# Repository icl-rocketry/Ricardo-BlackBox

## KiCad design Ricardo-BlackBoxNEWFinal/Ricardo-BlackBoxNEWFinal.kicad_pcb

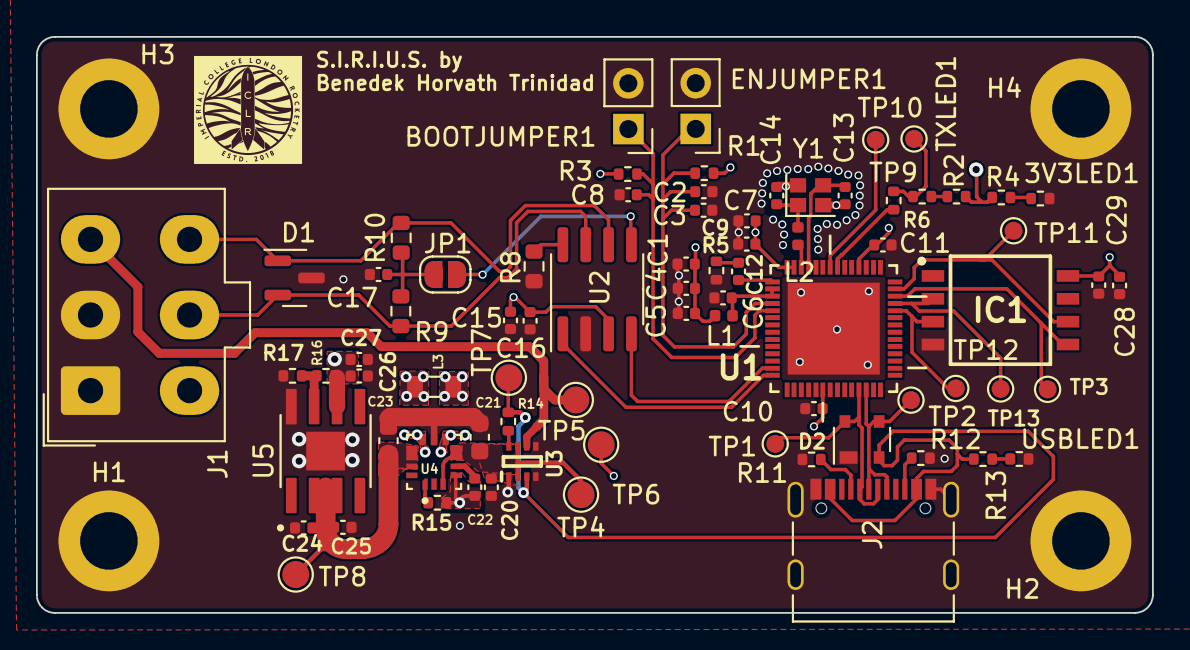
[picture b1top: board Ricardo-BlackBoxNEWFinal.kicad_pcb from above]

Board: 4 copper layers, 62.0 x 32.0 mm, 80 parts (0 on the bottom side), 41 nets.

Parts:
3V3LED1: 3V3LED; R_0402_1005Metric
BOOTJUMPER1: Conn_01x02_Male; PinHeader_1x02_P2.54mm_Vertical
C1, C16, C20, C24, C26, C28: 10uF; C_0402_1005Metric
C2, C4, C7, C22: 1uF; C_0402_1005Metric
C3, C5, C6, C8, C10, C11, C27, C29: 0.1uF; C_0402_1005Metric
C9: 10nF; C_0402_1005Metric
C12: 4.2pF; C_0402_1005Metric
C13, C14: 11pF; C_0402_1005Metric
C15: 100nF; C_0402_1005Metric
C17: 47nF; C_0402_1005Metric
C21: 10uF; C_0603_1608Metric
C23: 22uF; C_0603_1608Metric
C25: 4.7uF; C_0402_1005Metric
D1: SM712_SOT23; SOT-23
D2: SP0503BAHT; SOT-143
ENJUMPER1: Conn_01x02_Male; PinHeader_1x02_P2.54mm_Vertical
H1, H2, H3, H4: MountingHole_Pad; MountingHole_3.2mm_M3_DIN965_Pad
IC1: XTSD08GLGEAG; SON127P800X600X95-8N
J1: RBUS; Molex_Mini-Fit_Jr_5566-06A_2x03_P4.20mm_Vertical
J2: USB_C_Receptacle_USB2.0; USB_C_Receptacle_Palconn_UTC16-G
JP1: TermJP; SolderJumper-2_P1.3mm_Open_RoundedPad1.0x1.5mm
L1: 2.0nH; L_0402_1005Metric
L2: 20nH; L_0402_1005Metric
L3: 1uH; L_0805_2012Metric
R1, R3: 10K; R_0402_1005Metric
R2, R4, R13: 470; R_0402_1005Metric
R5: 47.5; R_0402_1005Metric
R6: 499; R_0402_1005Metric
R8: 0; R_0603_1608Metric
R9, R10: 60; R_0603_1608Metric
R11, R12: 5.1k; R_0402_1005Metric
R14, R17: 10k; R_0402_1005Metric
R15: 14k; R_0402_1005Metric
R16: 56k; R_0402_1005Metric
TP1, TP2, TP3, TP9, TP10, TP11, TP12, TP13: TestPoint; TestPoint_Pad_D1.0mm
TP4, TP5, TP6, TP7, TP8: TestPoint; TestPoint_Pad_D1.5mm
TXLED1: TX_LED; R_0402_1005Metric
U1: ESP32-S3; QFN40P700X700X90-57N
U2: SN65HVD230; SOIC-8_3.9x4.9mm_P1.27mm
U3: LM66200DRLR; SOTFL50P160X60-8N
U4: MAX77827AEFD+T; CONV_MAX77827AEFD+T
U5: SC4215; SOIC127P599X175-9N
USBLED1: USB_LED; R_0402_1005Metric
Y1: 40MHz±10ppm; Crystal_SMD_2016-4Pin_2.0x1.6mm

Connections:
+3V3: C1.1, C4.1, C5.1, C7.1, C9.1, C10.1, C11.1, C15.1, C16.1, C26.2, C27.2, C28.1, C29.1, IC1.8 (VDD), L1.1, R1.1, R2.1, R3.1, R4.2, R16.1, TP6.1, U1.20 (VDD3P3_RTC), U1.46 (VDD3P3_CPU), U1.55 (VDDA), U1.56 (VDDA), U2.3 (VCC), U5.6 (VOUT)
/BOOT: BOOTJUMPER1.1, C8.1, R3.2, U1.5 (GPIO0/BOOT)
/CAN+: D1.2 (A2), J1.5, R9.1, U2.7 (CANH)
/CAN-: D1.1 (A1), J1.6, R10.2, U2.6 (CANL)
/CAN-BUS/Vref: JP1.1 (A), U2.5 (Vref)
/CAN_RX: U1.13 (GPIO8/ADC1_CH7), U2.4 (R)
/CAN_TX: U1.14 (GPIO9/ADC1_CH8), U2.1 (D)
/CHIP_PU: C2.1, C3.1, ENJUMPER1.1, R1.2, U1.4 (CHIP_PU/RESET)
/CLK: IC1.3 (CLK), TP12.1, U1.38 (GPIO33)
/Data+: D2.3 (K), J2.A6 (D+), J2.B6 (D+), TP2.1, U1.26 (GPIO20/USB_D+/ADC2_CH9)
/Data-: D2.4 (K), J2.A7 (D-), J2.B7 (D-), TP1.1, U1.25 (GPIO19/USB_D-/ADC2_CH8)
/MISO: IC1.6 (SD0/DO), TP11.1, U1.41 (GPIO36)
/MOSI: IC1.5 (CMD/DI), TP3.1, U1.40 (GPIO35)
/NAND_CS: IC1.2 (SD3/CS), TP13.1, U1.39 (GPIO34)
/Power/BBIN: C20.1, C21.1, TP4.1, U3.2 (VOUT_1), U3.7 (VOUT_2), U4.3 (EN), U4.6 (IN)
/Power/BBOUT: C23.1, C24.1, C25.1, TP8.1, U4.11 (OUT), U4.13 (OUTS), U5.2 (EN), U5.3 (VIN)
/Power/BIAS: C22.1, U4.5 (BIAS)
/Power/FBIn: R16.2, R17.1, U5.7 (ADJ)
/Power/LX1: L3.1, U4.8 (LX1)
/Power/LX2: L3.2, U4.10 (LX2)
/Power/SEL: R15.1, U4.1 (SEL)
/RXD: TP10.1, U1.50 (U0RXD/PROG/GPIO44)
/TXD: R6.1, TP9.1, TXLED1.1 (K)
GND: 3V3LED1.1 (K), BOOTJUMPER1.2, C1.2, C2.2, C3.2, C4.2, C5.2, C6.2, C7.2, C8.2, C9.2, C10.2, C11.2, C13.2, C14.2, C15.2, C16.2, C17.2, C20.2, C21.2, C22.2, C23.2, C24.2, C25.2, C26.1, C27.1, C28.2, C29.2, D1.3 (common), D2.1 (A), ENJUMPER1.2, H1.1, H2.1, H3.1, H4.1, IC1.4 (GND), J1.1, J1.2, J2.A1 (GND), J2.A12 (GND), J2.B1 (GND), J2.B12 (GND), J2.S1 (SHIELD), R5.1, R8.2, R11.2, R12.1, R15.2, R17.2, U1.57 (GND), U2.2 (GND), U3.1 (GND_1), U3.4 (~ON), U3.5 (GND_2), U4.4 (AGND), U4.9 (PGND), U5.8 (GND), U5.9 (GND), USBLED1.1 (K), Y1.2, Y1.4
unnamed: 3V3LED1.2 (A), R4.1
unnamed: C6.1, L1.2, U1.2 (VDD3P3), U1.3 (VDD3P3)
unnamed: C12.1, R5.2
unnamed: C14.1, L2.2, Y1.1
unnamed: J2.A5 (CC1), R11.1
unnamed: J2.B5 (CC2), R12.2
unnamed: C17.1, JP1.2 (B), R9.2, R10.1
unnamed: R2.2, TXLED1.2 (A)
unnamed: C12.2, U1.1 (LNA_IN/RF)
unnamed: R6.2, U1.49 (U0TXD/PROG/GPIO43)
unnamed: C13.1, U1.53 (XTAL_N), Y1.3
unnamed: L2.1, U1.54 (XTAL_P)
unnamed: R8.1, U2.8 (Rs)
unnamed: R14.2, U3.8 (ST)
unnamed: R13.2, USBLED1.2 (A)
RBUS_uC_V: J1.3, TP5.1, U3.6 (VIN2)
VBUS: D2.2 (K), J2.A4 (VBUS), J2.A9 (VBUS), J2.B4 (VBUS), J2.B9 (VBUS), R13.1, R14.1, TP7.1, U3.3 (VIN1)

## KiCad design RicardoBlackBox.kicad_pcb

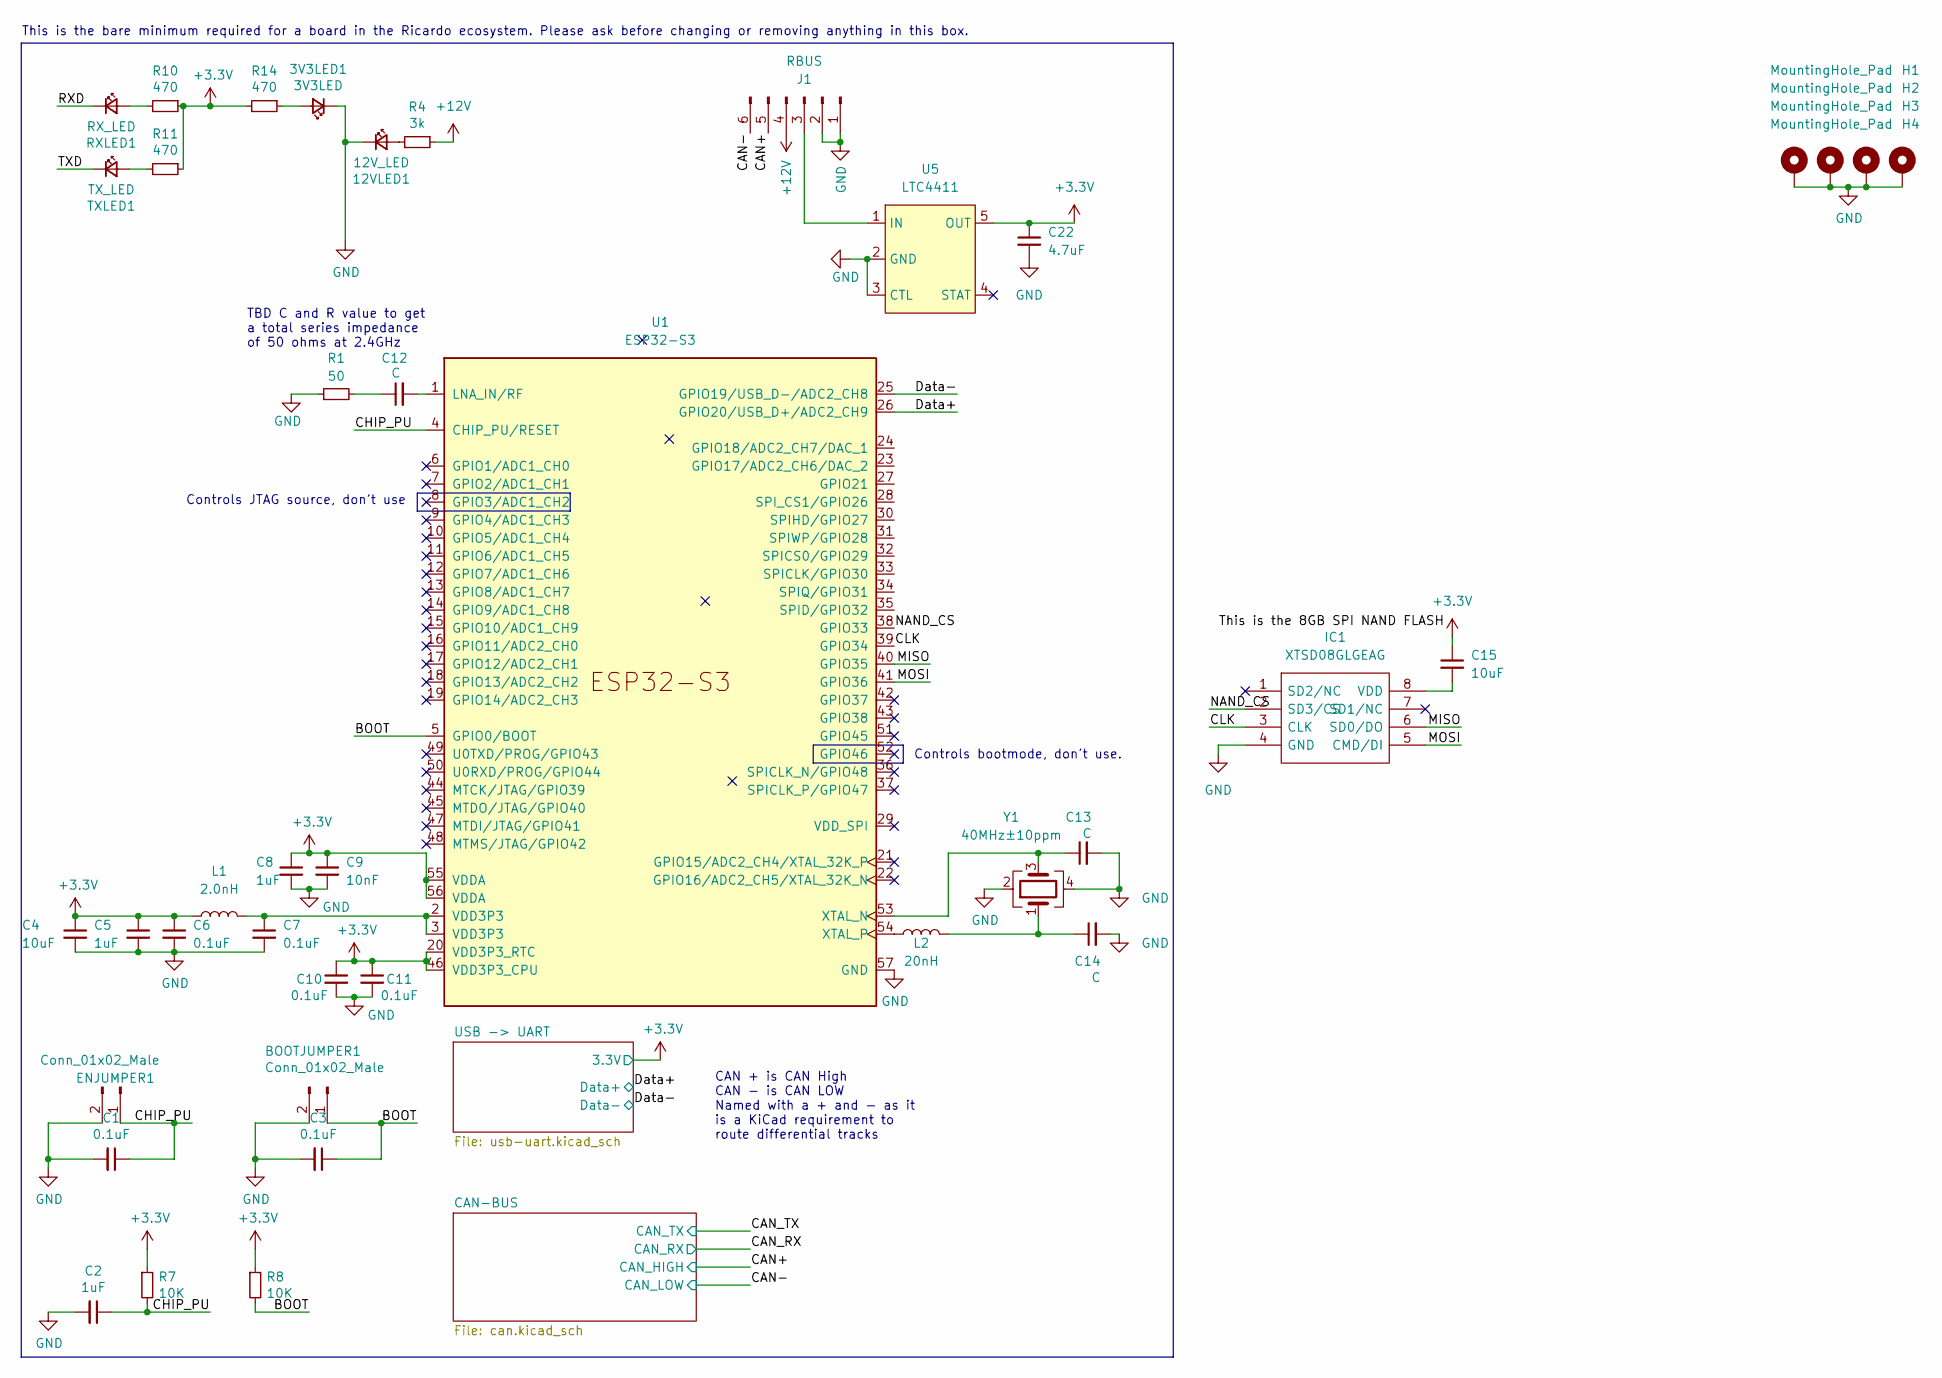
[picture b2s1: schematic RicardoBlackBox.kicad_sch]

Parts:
3V3LED1: 3V3LED; R_0402_1005Metric
12VLED1: 12V_LED; R_0402_1005Metric
BOOTJUMPER1: Conn_01x02_Male; PinHeader_1x02_P2.54mm_Vertical
C1, C3, C6, C7, C10, C11: 0.1uF; C_0402_1005Metric
C2, C5, C8: 1uF; C_0402_1005Metric
C4, C15: 10uF; C_0402_1005Metric
C9: 10nF; C_0402_1005Metric
C12, C13, C14: C; C_0603_1608Metric
C22: 4.7uF; C_0603_1608Metric
ENJUMPER1: Conn_01x02_Male; PinHeader_1x02_P2.54mm_Vertical
H1, H2, H3, H4: MountingHole_Pad; MountingHole_3.2mm_M3_DIN965_Pad
IC1: XTSD08GLGEAG; SON127P800X600X95-8N; Manufacturer_Part_Number XTSD08GLGEAG
J1: RBUS; Molex_Mini-Fit_Jr_5566-06A_2x03_P4.20mm_Vertical
L1: 2.0nH
L2: 20nH
R1: 50
R4: 3k; R_0402_1005Metric
R7, R8: 10K; R_0402_1005Metric
R10, R11, R14: 470; R_0402_1005Metric
RXLED1: RX_LED; LED_0603_1608Metric
TXLED1: TX_LED; R_0402_1005Metric
U1: ESP32-S3; QFN-56-1EP_7x7mm_P0.4mm_EP5.6x5.6mm
U5: LTC4411; SOT-23-5
Y1: 40MHz±10ppm; Crystal_SMD_2016-4Pin_2.0x1.6mm

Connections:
+3V3: C4.1, C5.1, C6.1, C8.1, C9.1, C10.1, C11.1, C15.1, C22.1, L1.1, R7.1, R8.1, R10.1, R11.1, R14.2, U1.20 (VDD3P3_RTC), U1.46 (VDD3P3_CPU), U1.55 (VDDA), U1.56 (VDDA), U5.5 (OUT); also elsewhere on the board
+12V: J1.4, R4.1
/BOOT: BOOTJUMPER1.1, C3.1, R8.2, U1.5 (GPIO0/BOOT)
/CAN+: J1.5; also elsewhere on the board
/CAN-: J1.6; also elsewhere on the board
/CHIP_PU: C1.1, C2.1, ENJUMPER1.1, R7.2, U1.4 (CHIP_PU/RESET)
/CLK: IC1.3 (CLK), U1.39 (GPIO34)
/Data+: U1.26 (GPIO20/USB_D+/ADC2_CH9); also elsewhere on the board
/Data-: U1.25 (GPIO19/USB_D-/ADC2_CH8); also elsewhere on the board
/MISO: IC1.6 (SD0/DO), U1.40 (GPIO35)
/MOSI: IC1.5 (CMD/DI), U1.41 (GPIO36)
/NAND_CS: IC1.2 (SD3/CS), U1.38 (GPIO33)
/RXD: RXLED1.1 (K)
/TXD: TXLED1.1 (K)
GND: 3V3LED1.1 (K), 12VLED1.1 (K), BOOTJUMPER1.2, C1.2, C2.2, C3.2, C4.2, C5.2, C6.2, C7.2, C8.2, C9.2, C10.2, C11.2, C13.2, C14.2, C22.2, ENJUMPER1.2, H1.1, H2.1, H3.1, H4.1, IC1.4 (GND), J1.1, J1.2, R1.1, U1.57 (GND), U5.2 (GND), U5.3 (CTL), Y1.2, Y1.4; also elsewhere on the board
unnamed: 3V3LED1.2 (A), R14.1
unnamed: 12VLED1.2 (A), R4.2
unnamed: C7.1, L1.2, U1.2 (VDD3P3), U1.3 (VDD3P3)
unnamed: C12.1, R1.2
unnamed: C12.2, U1.1 (LNA_IN/RF)
unnamed: C13.1, U1.53 (XTAL_N), Y1.3
unnamed: C14.1, L2.2, Y1.1
unnamed: C15.2, IC1.8 (VDD)
unnamed: J1.3, U5.1 (IN)
unnamed: L2.1, U1.54 (XTAL_P)
unnamed: R10.2, RXLED1.2 (A)
unnamed: R11.2, TXLED1.2 (A)

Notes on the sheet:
Controls bootmode, don't use.
This is the bare minimum required for a board in the Ricardo ecosystem. Please ask before changing or removing anything in this box.
TBD C and R value to get a total series impedance of 50 ohms at 2.4GHz
CAN + is CAN High CAN - is CAN LOW Named with a + and - as it is a KiCad requirement to route differential tracks
Controls JTAG source, don't use

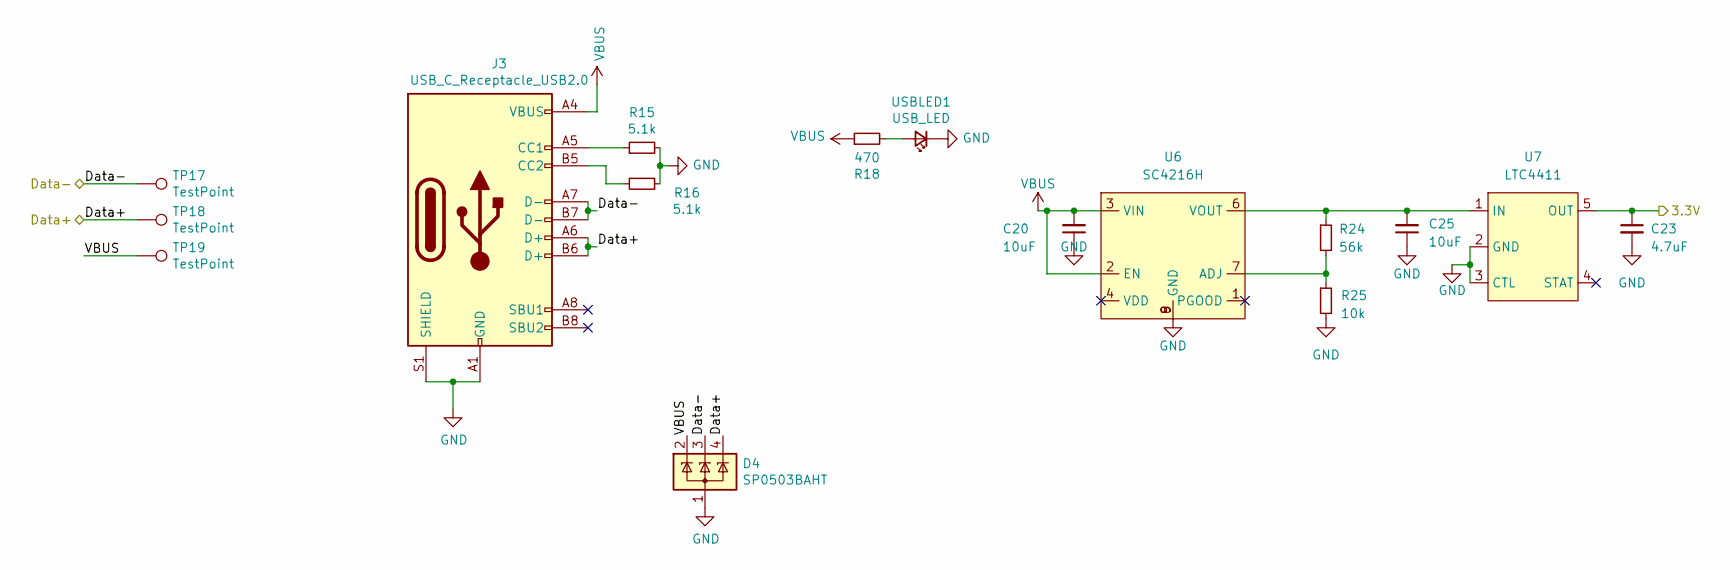
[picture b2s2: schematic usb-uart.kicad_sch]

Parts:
C20, C25: 10uF; C_0603_1608Metric
C23: 4.7uF; C_0603_1608Metric
D4: SP0503BAHT; SOT-143
J3: USB_C_Receptacle_USB2.0; USB_C_Receptacle_GCT_USB4085
R15, R16: 5.1k; R_0402_1005Metric
R18: 470; R_0402_1005Metric
R24: 56k; R_0402_1005Metric
R25: 10k; R_0402_1005Metric
TP17, TP18, TP19: TestPoint; TestPoint_Pad_D1.0mm
U6: SC4216H; SOIC127P599X175-9N
U7: LTC4411; SOT-23-5
USBLED1: USB_LED; LED_0603_1608Metric

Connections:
+3V3: C23.1, U7.5 (OUT); also elsewhere on the board
/Data+: D4.4 (K), J3.A6 (D+), J3.B6 (D+), TP18.1; also elsewhere on the board
/Data-: D4.3 (K), J3.A7 (D-), J3.B7 (D-), TP17.1; also elsewhere on the board
GND: C20.1, C23.2, C25.1, D4.1 (A), J3.A1 (GND), J3.A12 (GND), J3.B1 (GND), J3.B12 (GND), J3.S1 (SHIELD), R15.2, R16.1, R25.2, U6.8 (GND), U6.9 (GND), U7.2 (GND), U7.3 (CTL), USBLED1.1 (K); also elsewhere on the board
unnamed: C25.2, R24.1, U6.6 (VOUT), U7.1 (IN)
unnamed: J3.A5 (CC1), R15.1
unnamed: J3.B5 (CC2), R16.2
unnamed: R18.2, USBLED1.2 (A)
unnamed: R24.2, R25.1, U6.7 (ADJ)
VBUS: C20.2, D4.2 (K), J3.A4 (VBUS), J3.A9 (VBUS), J3.B4 (VBUS), J3.B9 (VBUS), R18.1, TP19.1, U6.2 (EN), U6.3 (VIN)

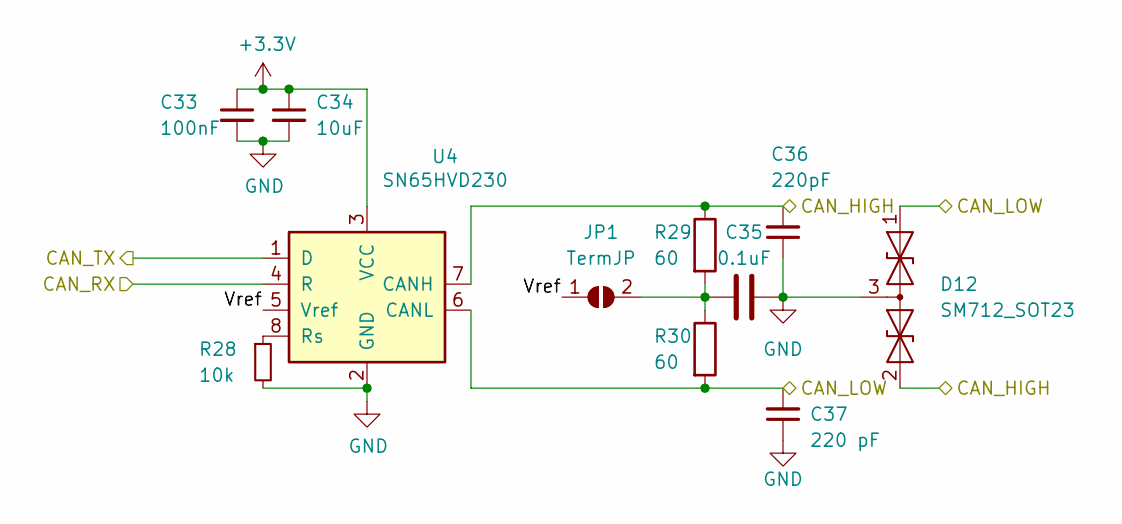
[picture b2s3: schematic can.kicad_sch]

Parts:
C33: 100nF; C_0402_1005Metric
C34: 10uF; C_0603_1608Metric
C35: 0.1uF; C_0402_1005Metric
C36: 220pF; C_0402_1005Metric
C37: 220 pF; C_0402_1005Metric
D12: SM712_SOT23; SOT-23
JP1: TermJP
R28: 10k; R_0402_1005Metric
R29, R30: 60; R_0402_1005Metric
U4: SN65HVD230; SOIC-8_3.9x4.9mm_P1.27mm

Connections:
+3V3: C33.1, C34.1, U4.3 (VCC); also elsewhere on the board
/CAN+: C36.2, D12.2 (A2), R29.1, U4.7 (CANH); also elsewhere on the board
/CAN-: C37.2, D12.1 (A1), R30.2, U4.6 (CANL); also elsewhere on the board
/CAN-BUS/Vref: JP1.1 (A), U4.5 (Vref)
/CAN_RX: U4.4 (R)
/CAN_TX: U4.1 (D)
GND: C33.2, C34.2, C35.2, C36.1, C37.1, D12.3 (common), R28.2, U4.2 (GND); also elsewhere on the board
unnamed: C35.1, JP1.2 (B), R29.2, R30.1
unnamed: R28.1, U4.8 (Rs)

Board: 2 copper layers, 62 parts (0 on the bottom side), 26 nets, no tracks yet.

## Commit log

2022-11-12 PushingFirstSchematic
2022-11-12 PushingSecondSchematic
2022-11-15 push3schematicandpcb
2022-11-29 NewESP32RicardoBlackBox
2022-12-13 AsOf13/12/2022
2023-01-31 AsOf31/01/2023
    Schematic should be done, PCB beginning to be done
2023-04-12 AsOf12/04/2023
2023-06-03 RicardoBlackBox03_06_2023
2023-06-03 03/06/2023RicardoBlackBoxAfterICLRMeeting
    13:31
2023-06-10 10_06_2023BlackBox
    All files for Black Box needed are in this
2023-06-20 Black_Box_20/06/2023_THIS_HAS_ALL_FOLDER_HAS_FILES
    This folder has the board up to date
2023-06-20 BlackBox_20_06_2023_ThisFolderHasAllTheFilesNeeded
2023-07-30 RicardoBlackBox_30_07_2023
2023-08-13 RicardoBlackBoxNEWFinal_13_08_2023
2023-08-14 Ricardo-BlackBoxNEWFinal_14_08_2023
2023-08-15 Ricardo-BlackBoxFinal_15_08_2023
2023-08-15 RicardoBlackBoxFinal(2)_15_08_2023
2023-08-15 RicardoBlackBoxFinal_15_08_2023_(3)
2023-08-15 RicardoBlackBox_15_08_2023_(4)
2023-08-20 RicardoBlackBoxFinal_20_08_2023
2023-08-20 RicardoBlackBox_20_08_2023(2)
2023-08-20 RicardoBlackBox_20_08_2023(3)
2023-08-21 RicardoBlackBox_21_08_2023
    Changed some silkscreens and removed some disconnected tracks
2023-09-05 ordering
2023-09-29 CreatedFirmwareFolder
    Copied Ricardo-OSTemplate to Ricardo-BlackBox
2023-09-29 z
    sorted into hardware and firmware
2023-10-10 FirmwareEUROC
